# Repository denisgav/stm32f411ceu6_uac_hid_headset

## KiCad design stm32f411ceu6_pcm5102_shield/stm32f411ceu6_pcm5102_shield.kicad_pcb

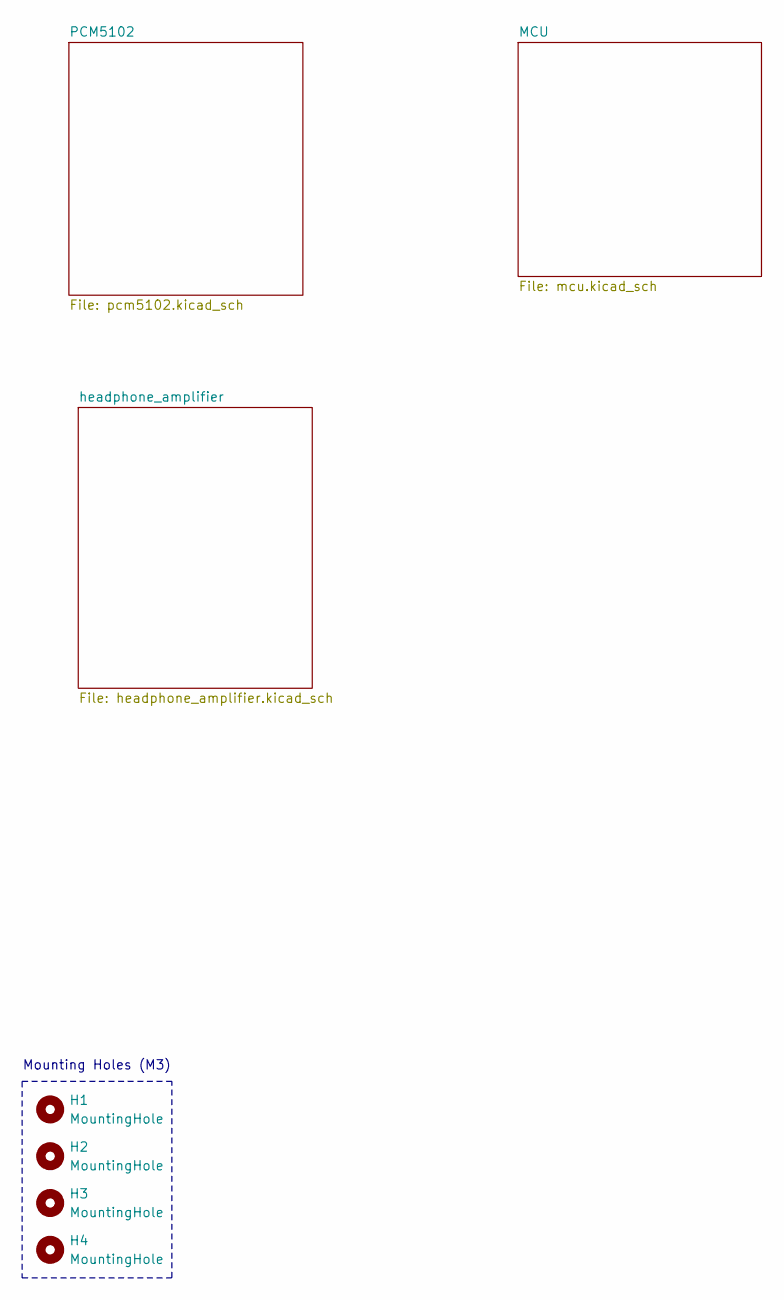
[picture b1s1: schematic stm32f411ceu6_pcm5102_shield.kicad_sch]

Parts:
H1, H2, H3, H4: MountingHole; MountingHole_3.2mm_M3

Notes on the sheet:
Mounting Holes (M3)

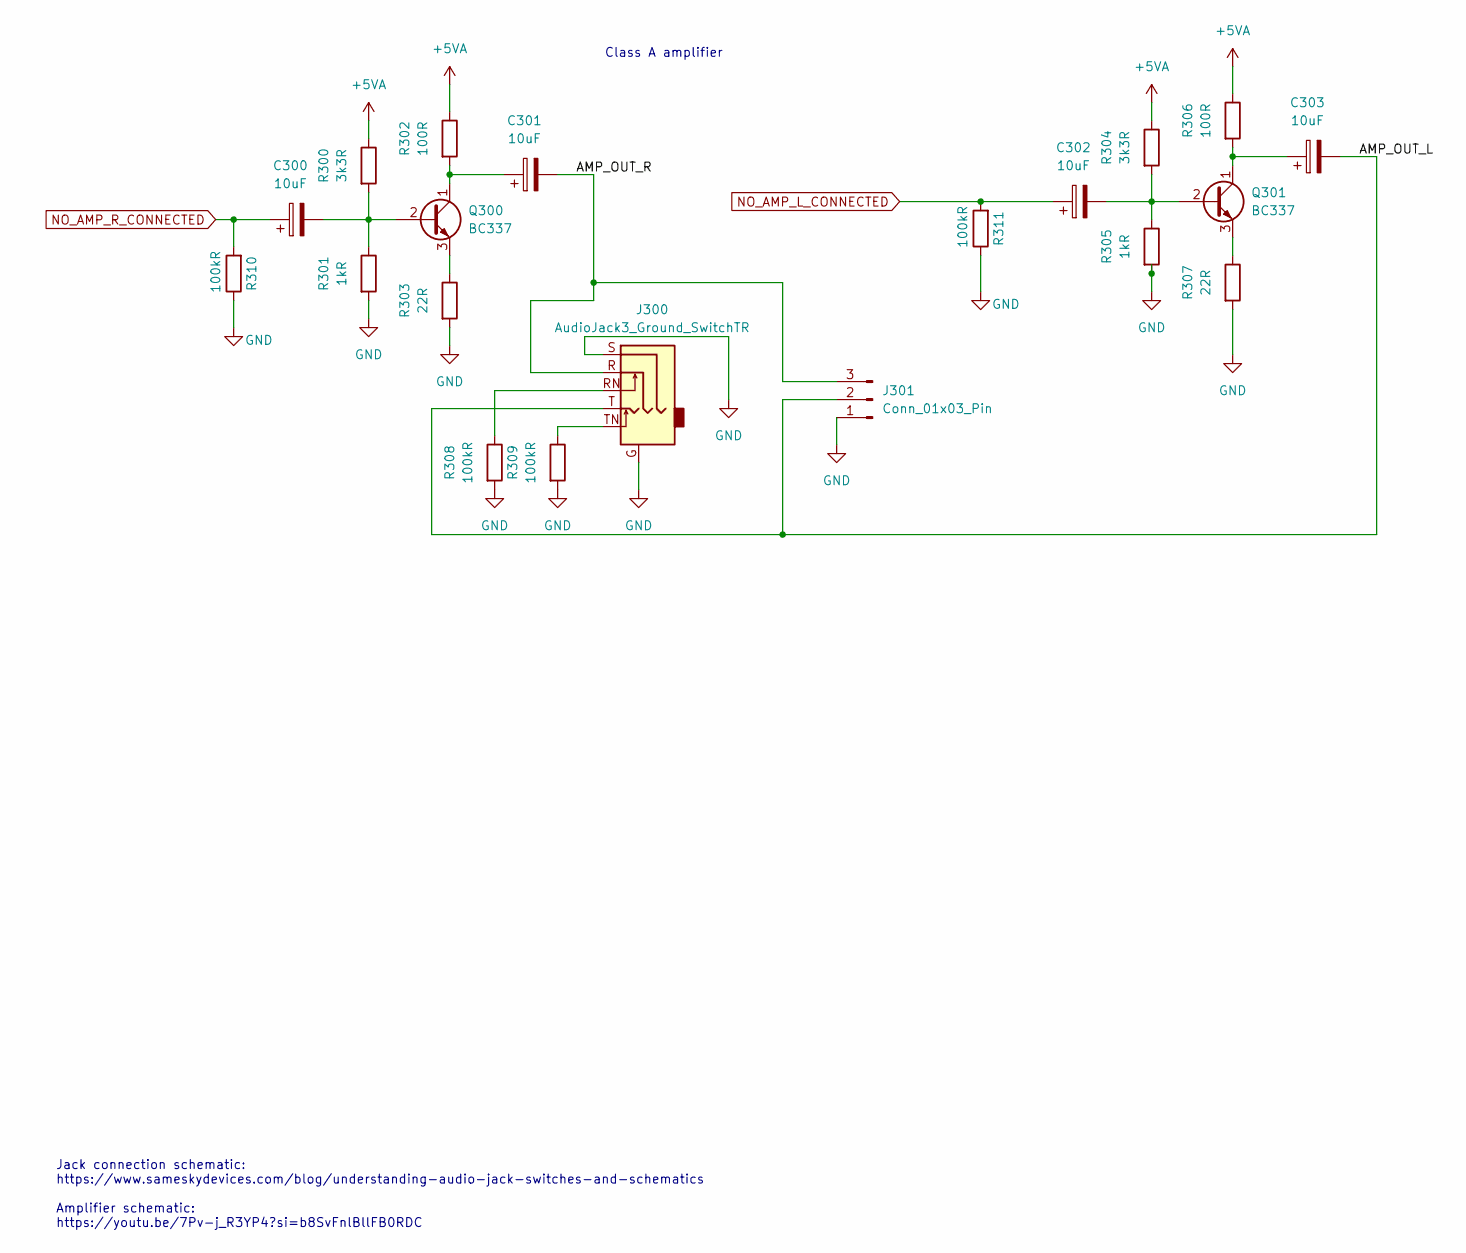
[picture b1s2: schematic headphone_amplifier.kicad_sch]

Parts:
C300, C301, C302, C303: 10uF; CP_EIA-3216-18_Kemet-A; Manufacturer Part Number TAJA106K016RNJ
J300: AudioJack3_Ground_SwitchTR; AudioJack_3.5mm_PJ311
J301: Conn_01x03_Pin; PinHeader_1x03_P2.54mm_Vertical
Q300, Q301: BC337; TO-92_Inline; Manufacturer Part Number LGE BC337-40
R300, R304: 3k3R; R_0805_2012Metric; Manufacturer Part Number 0805W8F3301T5E
R301, R305: 1kR; R_0805_2012Metric; Manufacturer Part Number 0805W8F1001T5E
R302, R306: 100R; R_0805_2012Metric; Manufacturer Part Number 0805W8F1000T5E
R303, R307: 22R; R_0603_1608Metric; Manufacturer Part Number 0603WAF220JT5E
R308, R309, R310, R311: 100kR; R_0805_2012Metric; Manufacturer Part Number 0805W8J0104T5E

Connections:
+5VA: R300.1, R302.1, R304.1, R306.1; also elsewhere on the board
/headphone_amplifier/AMP_OUT_L: C303.2, J300.T, J301.2
/headphone_amplifier/AMP_OUT_R: C301.2, J300.R, J301.3
GND: J300.G, J300.S, J301.1, R301.2, R303.2, R305.2, R307.2, R308.2, R309.2, R310.1, R311.1; also elsewhere on the board
NO_AMP_L_CONNECTED: C302.1, R311.2; also elsewhere on the board
NO_AMP_R_CONNECTED: C300.1, R310.2; also elsewhere on the board
unnamed: J300.RN, R308.1
unnamed: J300.TN, R309.1
unnamed: C300.2, Q300.2 (B), R300.2, R301.1
unnamed: C301.1, Q300.1 (C), R302.2
unnamed: Q300.3 (E), R303.1
unnamed: C302.2, Q301.2 (B), R304.2, R305.1
unnamed: C303.1, Q301.1 (C), R306.2
unnamed: Q301.3 (E), R307.1

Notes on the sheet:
Jack connection schematic: https://www.sameskydevices.com/blog/understanding-audio-jack-switches-and-schematics Amplifier schematic: https://youtu.be/7Pv-j_R3YP4?si=b8SvFnlBllFB0RDC
Class A amplifier

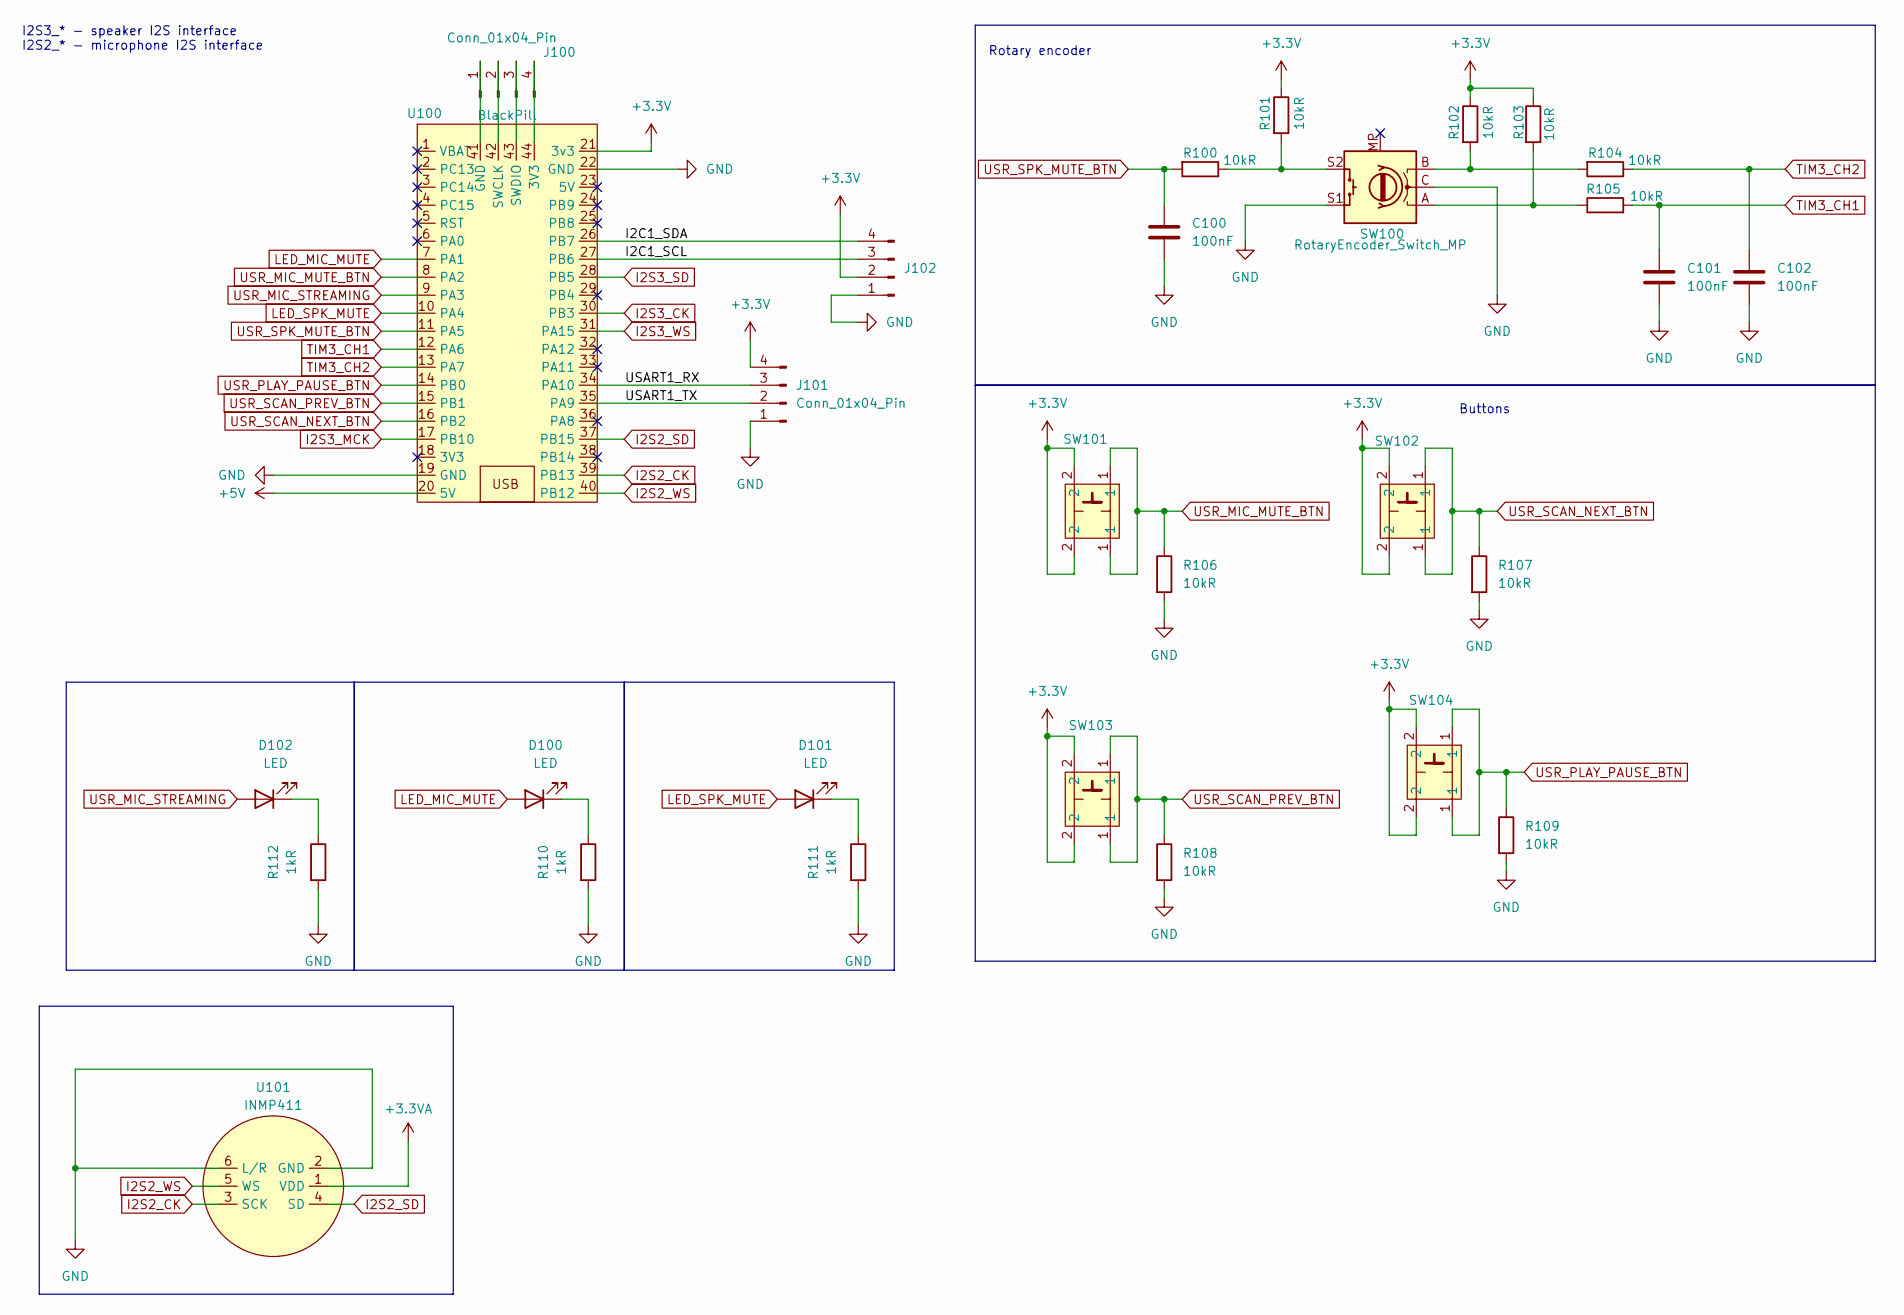
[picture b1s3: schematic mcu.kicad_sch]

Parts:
C100, C101, C102: 100nF; C_0402_1005Metric; Manufacturer Part Number CL05B104KO5NNNC
D100, D101, D102: LED; LED_D3.0mm
J100, J101, J102: Conn_01x04_Pin; PinHeader_1x04_P2.54mm_Vertical
R100, R101, R102, R103, R104, R105: 10kR; R_0805_2012Metric; Manufacturer Part Number 0805W8J0103T5E
R106, R107, R108, R109: 10kR; R_0805_2012Metric; Manufacturer Part Number 0805W8J0103T5E; DigiKey Part Number 1276-3431-6-ND
R110, R111, R112: 1kR; R_0805_2012Metric; Manufacturer Part Number 0805W8F1001T5E
SW100: RotaryEncoder_Switch_MP; RotaryEncoder_Alps_EC12E-Switch_Vertical_H20mm
SW101, SW102, SW103, SW104: SW_PUSH_6mm_H5mm
U100: BlackPill; stm32f411_blackpill
U101: INMP411; inmp441

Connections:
+3.3V: J101.4, J102.2, R101.1, R102.1, R103.1, SW101.2, SW102.2, SW103.2, SW104.2, U100.21 (3v3); also elsewhere on the board
+3.3VA: U101.1 (VDD); also elsewhere on the board
+5V: U100.20 (5V); also elsewhere on the board
/MCU/I2C1_SCL: J102.3, U100.27 (PB6)
/MCU/I2C1_SDA: J102.4, U100.26 (PB7)
/MCU/USART1_RX: J101.3, U100.34 (PA10)
/MCU/USART1_TX: J101.2, U100.35 (PA9)
GND: C100.2, C101.2, C102.2, J101.1, J102.1, R106.2, R107.2, R108.2, R109.2, R110.2, R111.2, R112.2, SW100.C, SW100.S1, U100.19 (GND), U100.22 (GND), U101.2 (GND), U101.6 (L/R); also elsewhere on the board
I2S2_CK: U100.39 (PB13), U101.3 (SCK)
I2S2_SD: U100.37 (PB15), U101.4 (SD)
I2S2_WS: U100.40 (PB12), U101.5 (WS)
I2S3_CK: U100.30 (PB3); also elsewhere on the board
I2S3_MCK: U100.17 (PB10); also elsewhere on the board
I2S3_SD: U100.28 (PB5); also elsewhere on the board
I2S3_WS: U100.31 (PA15); also elsewhere on the board
LED_MIC_MUTE: D100.2 (A), U100.7 (PA1)
LED_SPK_MUTE: D101.2 (A), U100.10 (PA4)
unnamed: D100.1 (K), R110.1
unnamed: D101.1 (K), R111.1
unnamed: D102.1 (K), R112.1
unnamed: J100.1, U100.41 (GND)
unnamed: J100.2, U100.42 (SWCLK)
unnamed: J100.3, U100.43 (SWDIO)
unnamed: J100.4, U100.44 (3V3)
unnamed: R100.1, R101.2, SW100.S2
unnamed: R102.2, R104.2, SW100.B
unnamed: R103.2, R105.1, SW100.A
TIM3_CH1: C101.1, R105.2, U100.12 (PA6)
TIM3_CH2: C102.1, R104.1, U100.13 (PA7)
USR_MIC_MUTE_BTN: R106.1, SW101.1, U100.8 (PA2)
USR_MIC_STREAMING: D102.2 (A), U100.9 (PA3)
USR_PLAY_PAUSE_BTN: R109.1, SW104.1, U100.14 (PB0)
USR_SCAN_NEXT_BTN: R107.1, SW102.1, U100.16 (PB2)
USR_SCAN_PREV_BTN: R108.1, SW103.1, U100.15 (PB1)
USR_SPK_MUTE_BTN: C100.1, R100.2, U100.11 (PA5)

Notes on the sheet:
Rotary encoder
Buttons
I2S3_* - speaker I2S interface I2S2_* - microphone I2S interface

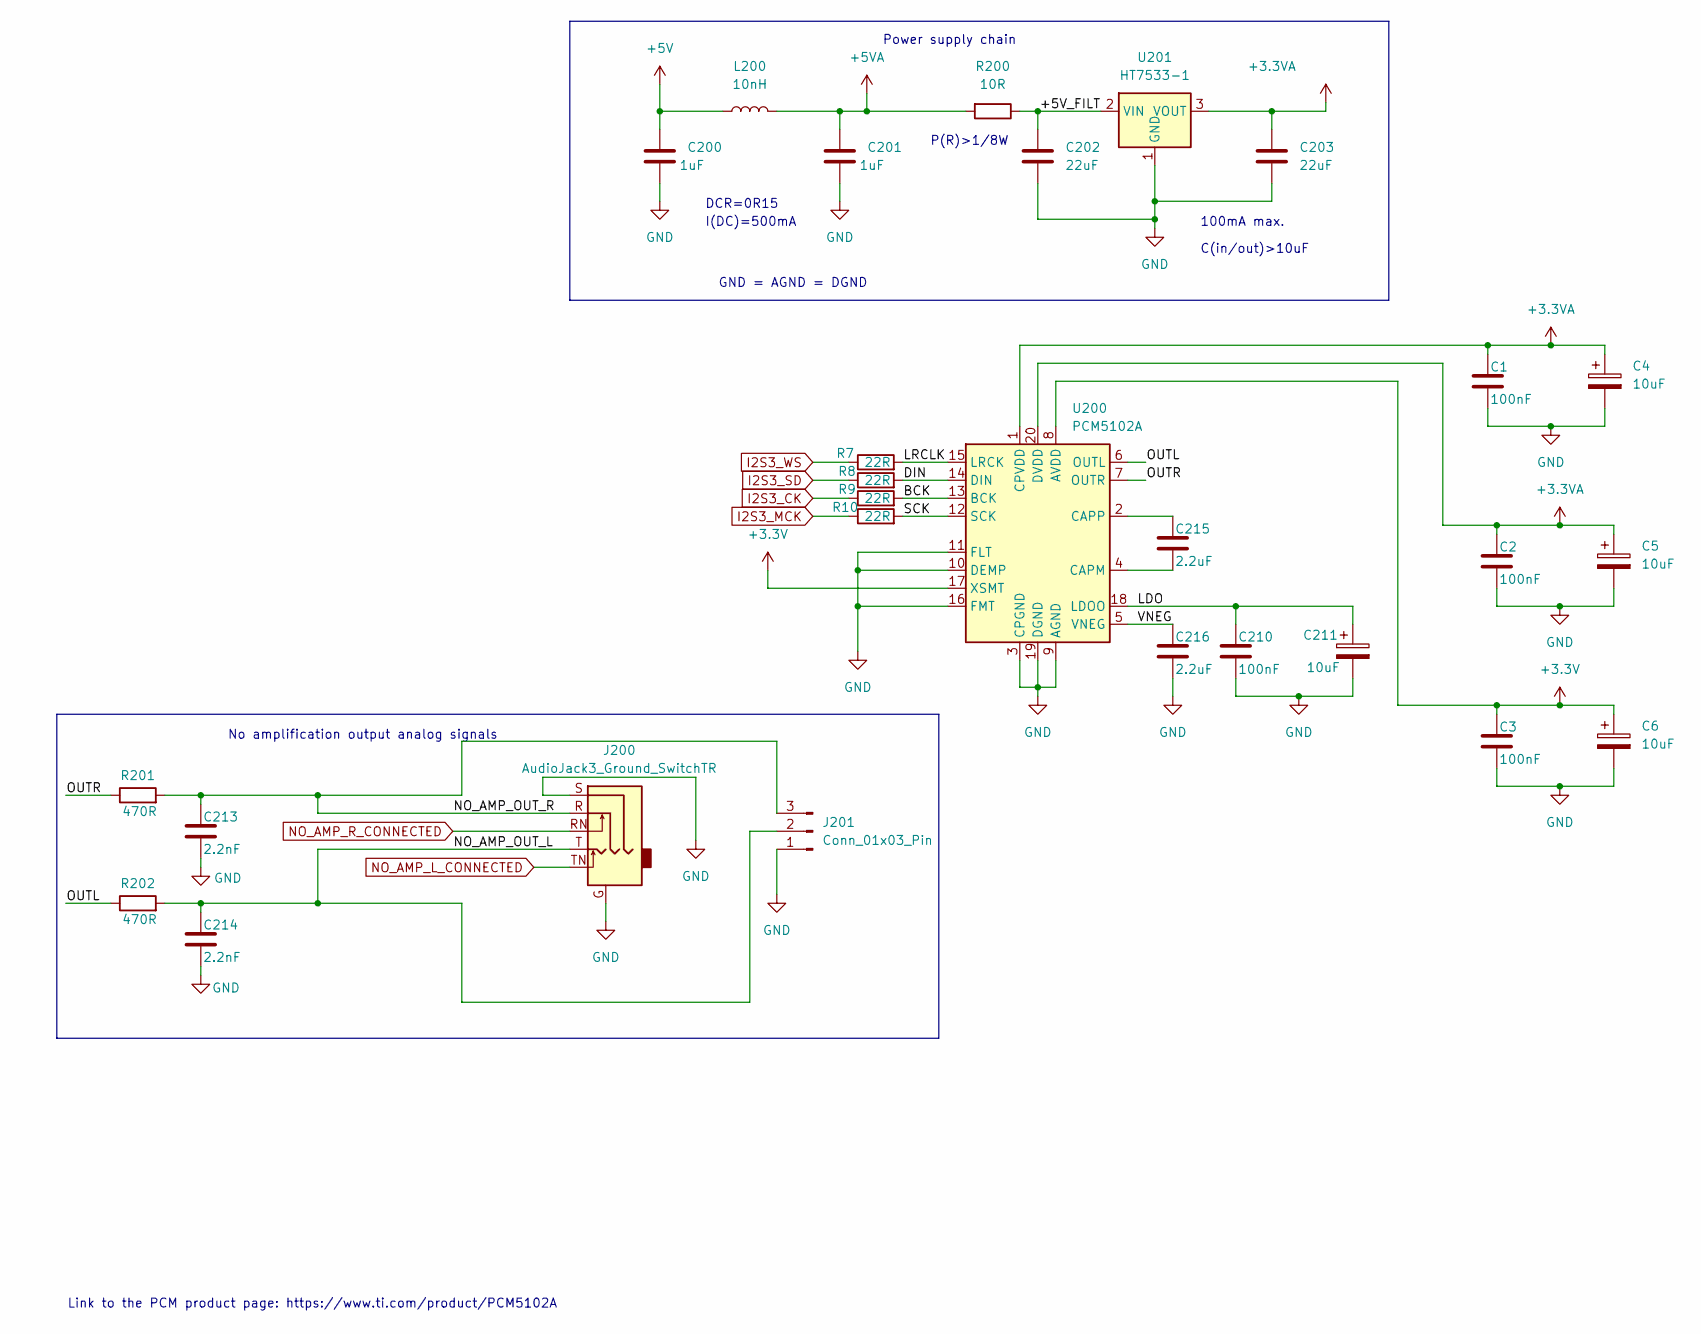
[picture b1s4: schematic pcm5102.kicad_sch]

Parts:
C1, C2, C3, C210: 100nF; C_0402_1005Metric; Manufacturer Part Number CL05B104KO5NNNC
C4, C5, C6, C211: 10uF; CP_EIA-3216-18_Kemet-A; Manufacturer Part Number TAJA106K016RNJ
C200, C201: 1uF; C_0805_2012Metric; Manufacturer Part Number CL21B105KBFNNNE
C202, C203: 22uF; C_0805_2012Metric; Manufacturer Part Number CL21A226MQQNNNE
C213, C214: 2.2nF; C_0805_2012Metric; Manufacturer Part Number CL21C222JBFNNNE
C215, C216: 2.2uF; C_0805_2012Metric; Manufacturer Part Number CL21B225KAFNNNE
J200: AudioJack3_Ground_SwitchTR; AudioJack_3.5mm_PJ311
J201: Conn_01x03_Pin; PinHeader_1x03_P2.54mm_Vertical
L200: 10nH; L_0402_1005Metric; Manufacturer Part Number CGA2B3X7R1H103M050BE
R7, R8, R9, R10: 22R; R_0603_1608Metric; Manufacturer Part Number 0603WAF220JT5E
R200: 10R; R_0805_2012Metric; Manufacturer Part Number 0805W8F100JT5E
R201, R202: 470R; R_0805_2012Metric; Manufacturer Part Number 0805W8F4700T5E
U200: PCM5102A; TSSOP-20_4.4x6.5mm_P0.65mm
U201: HT7533-1; SOT-89-3; Manufacturer Part Number HT7533-1

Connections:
+3.3V: C3.1, C6.1, U200.8 (AVDD), U200.17 (XSMT); also elsewhere on the board
+3.3VA: C1.1, C2.1, C4.1, C5.1, C203.1, U200.1 (CPVDD), U200.20 (DVDD), U201.3 (VOUT); also elsewhere on the board
+5V: C200.1, L200.1; also elsewhere on the board
+5VA: C201.1, L200.2, R200.2; also elsewhere on the board
/PCM5102/+5V_FILT: C202.1, R200.1, U201.2 (VIN)
/PCM5102/BCK: R9.2, U200.13 (BCK)
/PCM5102/DIN: R8.2, U200.14 (DIN)
/PCM5102/LDO: C210.1, C211.1, U200.18 (LDOO)
/PCM5102/LRCLK: R7.2, U200.15 (LRCK)
/PCM5102/NO_AMP_OUT_L: C214.1, J200.T, J201.2, R202.2
/PCM5102/NO_AMP_OUT_R: C213.1, J200.R, J201.3, R201.2
/PCM5102/OUTL: R202.1, U200.6 (OUTL)
/PCM5102/OUTR: R201.1, U200.7 (OUTR)
/PCM5102/SCK: R10.2, U200.12 (SCK)
/PCM5102/VNEG: C216.1, U200.5 (VNEG)
GND: C1.2, C2.2, C3.2, C4.2, C5.2, C6.2, C200.2, C201.2, C202.2, C203.2, C210.2, C211.2, C213.2, C214.2, C216.2, J200.G, J200.S, J201.1, U200.3 (CPGND), U200.9 (AGND), U200.10 (DEMP), U200.11 (FLT), U200.16 (FMT), U200.19 (DGND), U201.1 (GND); also elsewhere on the board
I2S3_CK: R9.1; also elsewhere on the board
I2S3_MCK: R10.1; also elsewhere on the board
I2S3_SD: R8.1; also elsewhere on the board
I2S3_WS: R7.1; also elsewhere on the board
NO_AMP_L_CONNECTED: J200.TN; also elsewhere on the board
NO_AMP_R_CONNECTED: J200.RN; also elsewhere on the board
unnamed: C215.2, U200.4 (CAPM)
unnamed: C215.1, U200.2 (CAPP)

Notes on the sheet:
100mA max.
GND = AGND = DGND
DCR=0R15
C(in/out)>10uF
Link to the PCM product page: https://www.ti.com/product/PCM5102A
P(R)>1/8W
I(DC)=500mA
No amplification output analog signals
Power supply chain

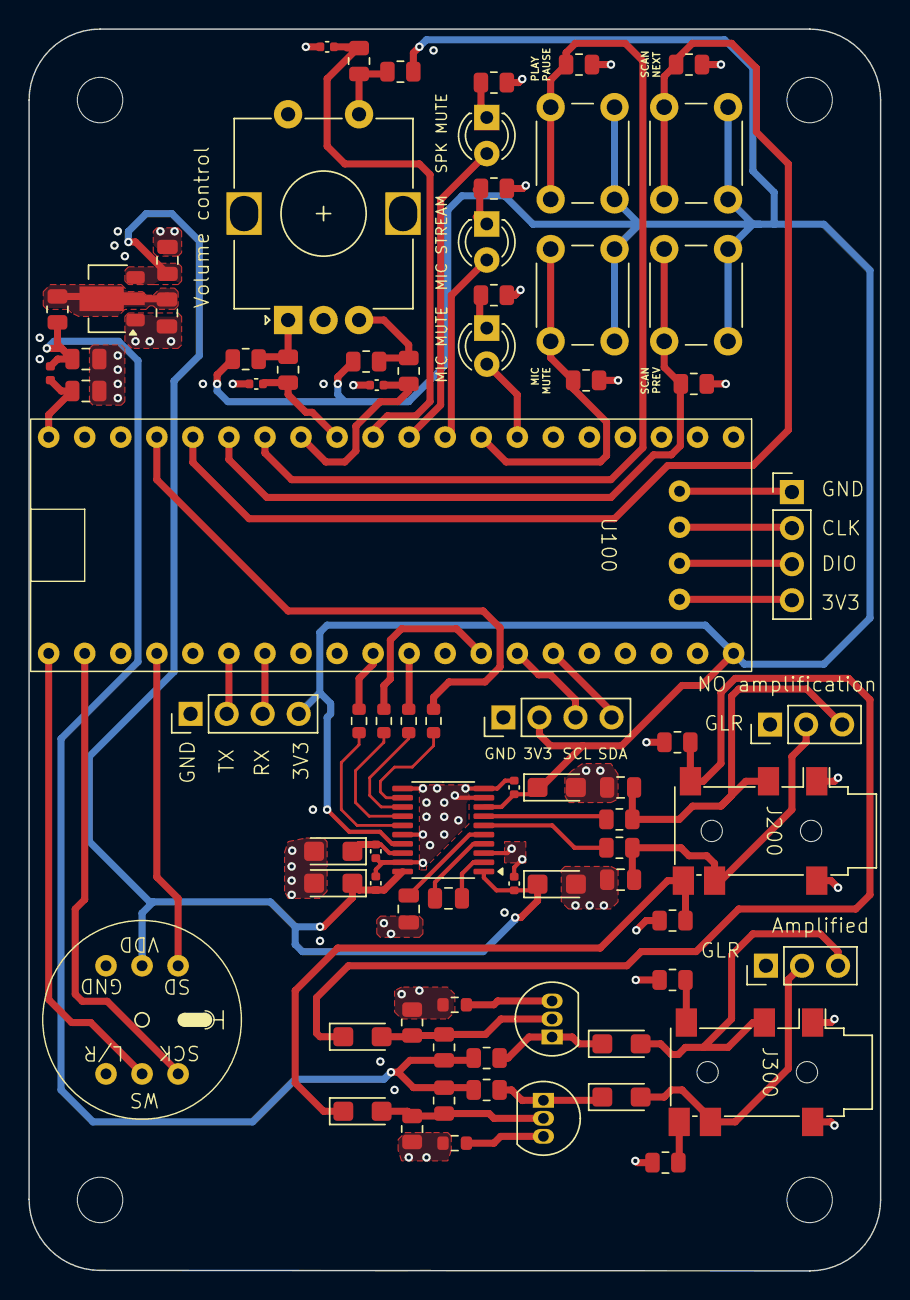
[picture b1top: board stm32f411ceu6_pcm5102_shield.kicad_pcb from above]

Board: 4 copper layers, 60.0 x 87.5 mm, 81 parts (0 on the bottom side), 61 nets.

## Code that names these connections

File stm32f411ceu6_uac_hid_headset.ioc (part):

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Mcu.Name=STM32F411C(C-E)Ux
Mcu.Package=UFQFPN48
Mcu.UserName=STM32F411CEUx
PA1.GPIOParameters=GPIO_Label
PA1.GPIO_Label=LED_MIC_MUTE
PA1.Signal=GPIO_Output
PA10.Mode=Asynchronous
PA10.Signal=USART1_RX
PA11.Mode=Device_Only
PA11.Signal=USB_OTG_FS_DM
PA12.Mode=Device_Only
PA12.Signal=USB_OTG_FS_DP
PA13.Mode=Serial_Wire
PA13.Signal=SYS_JTMS-SWDIO
PA14.Mode=Serial_Wire
PA14.Signal=SYS_JTCK-SWCLK
PA15.Mode=Half_Duplex_Master
PA15.Signal=I2S3_WS
PA2.GPIOParameters=GPIO_PuPd,GPIO_Label
PA2.GPIO_Label=USR_MIC_MUTE_BTN
PA2.GPIO_PuPd=GPIO_PULLDOWN
PA2.Signal=GPIO_Input
PA3.GPIOParameters=GPIO_Label
PA3.GPIO_Label=LED_MIC_STREAMING
PA3.Signal=GPIO_Output
PA4.GPIOParameters=GPIO_Label
PA4.GPIO_Label=LED_SPK_MUTE
PA4.Signal=GPIO_Output
PA5.GPIOParameters=GPIO_PuPd,GPIO_Label
PA5.GPIO_Label=USR_SPK_MUTE_BTN
PA5.GPIO_PuPd=GPIO_PULLUP
PA5.Signal=GPIO_Input
PA6.Signal=S_TIM3_CH1
PA7.Signal=S_TIM3_CH2
PA9.Mode=Asynchronous
PA9.Signal=USART1_TX
PB0.GPIOParameters=GPIO_PuPd,GPIO_Label
PB0.GPIO_Label=USR_PLAY_PAUSE_BTN
PB0.GPIO_PuPd=GPIO_PULLDOWN
PB0.Signal=GPIO_Input
PB1.GPIOParameters=GPIO_PuPd,GPIO_Label
PB1.GPIO_Label=USR_SCAN_PREV_BTN
PB1.GPIO_PuPd=GPIO_PULLDOWN
PB1.Signal=GPIO_Input
PB10.Mode=Master_Clock_Activated
PB10.Signal=I2S3_MCK
PB12.Mode=Half_Duplex_Master
PB12.Signal=I2S2_WS
PB13.Mode=Half_Duplex_Master
PB13.Signal=I2S2_CK
PB15.Mode=Half_Duplex_Master
PB15.Signal=I2S2_SD
PB2.GPIOParameters=GPIO_PuPd,GPIO_Label
PB2.GPIO_Label=USR_SCAN_NEXT_BTN
PB2.GPIO_PuPd=GPIO_PULLDOWN
PB2.Signal=GPIO_Input
PB3.Mode=Half_Duplex_Master
PB3.Signal=I2S3_CK
PB5.Mode=Half_Duplex_Master
PB5.Signal=I2S3_SD
PB6.Mode=I2C
PB6.Signal=I2C1_SCL
PB7.Mode=I2C
PB7.Signal=I2C1_SDA
PC13-ANTI_TAMP.GPIOParameters=GPIO_Label
PC13-ANTI_TAMP.GPIO_Label=ONBOARD_LED
PC13-ANTI_TAMP.Signal=GPIO_Output
PH0\ -\ OSC_IN.Mode=HSE-External-Oscillator
PH0\ -\ OSC_IN.Signal=RCC_OSC_IN
PH1\ -\ OSC_OUT.Mode=HSE-External-Oscillator
PH1\ -\ OSC_OUT.Signal=RCC_OSC_OUT
RCC.HSE_VALUE=25000000
RCC.SYSCLKFreq_VALUE=84000000
RCC.SYSCLKSource=RCC_SYSCLKSOURCE_PLLCLK
board=custom

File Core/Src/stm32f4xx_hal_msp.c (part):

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
    __HAL_RCC_GPIOB_CLK_ENABLE();
    /**I2C1 GPIO Configuration
    PB6     ------> I2C1_SCL
    PB7     ------> I2C1_SDA
    */
    GPIO_InitStruct.Pin = GPIO_PIN_6|GPIO_PIN_7;
    GPIO_InitStruct.Mode = GPIO_MODE_AF_OD;
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    __HAL_RCC_I2C1_CLK_DISABLE();

    /**I2C1 GPIO Configuration
    PB6     ------> I2C1_SCL
    PB7     ------> I2C1_SDA
    */
    HAL_GPIO_DeInit(GPIOB, GPIO_PIN_6);

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
    __HAL_RCC_GPIOB_CLK_ENABLE();
    /**I2S2 GPIO Configuration
    PB12     ------> I2S2_WS
    PB13     ------> I2S2_CK
    PB15     ------> I2S2_SD
    */
    GPIO_InitStruct.Pin = GPIO_PIN_12|GPIO_PIN_13|GPIO_PIN_15;
    GPIO_InitStruct.Mode = GPIO_MODE_AF_PP;
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    __HAL_RCC_GPIOB_CLK_ENABLE();
    __HAL_RCC_GPIOA_CLK_ENABLE();
    /**I2S3 GPIO Configuration
    PB10     ------> I2S3_MCK
    PA15     ------> I2S3_WS
    PB3     ------> I2S3_CK
    PB5     ------> I2S3_SD
    */
    GPIO_InitStruct.Pin = GPIO_PIN_10|GPIO_PIN_3|GPIO_PIN_5;
    GPIO_InitStruct.Mode = GPIO_MODE_AF_PP;
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    __HAL_RCC_SPI2_CLK_DISABLE();

    /**I2S2 GPIO Configuration
    PB12     ------> I2S2_WS
    PB13     ------> I2S2_CK
    PB15     ------> I2S2_SD
    */
    HAL_GPIO_DeInit(GPIOB, GPIO_PIN_12|GPIO_PIN_13|GPIO_PIN_15);

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    __HAL_RCC_SPI3_CLK_DISABLE();

    /**I2S3 GPIO Configuration
    PB10     ------> I2S3_MCK
    PA15     ------> I2S3_WS
    PB3     ------> I2S3_CK
    PB5     ------> I2S3_SD
    */
    HAL_GPIO_DeInit(GPIOB, GPIO_PIN_10|GPIO_PIN_3|GPIO_PIN_5);

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
    __HAL_RCC_GPIOA_CLK_ENABLE();
    /**TIM3 GPIO Configuration
    PA6     ------> TIM3_CH1
    PA7     ------> TIM3_CH2
    */
    GPIO_InitStruct.Pin = GPIO_PIN_6|GPIO_PIN_7;
    GPIO_InitStruct.Mode = GPIO_MODE_AF_PP;
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    __HAL_RCC_TIM3_CLK_DISABLE();

    /**TIM3 GPIO Configuration
    PA6     ------> TIM3_CH1
    PA7     ------> TIM3_CH2
    */
    HAL_GPIO_DeInit(GPIOA, GPIO_PIN_6|GPIO_PIN_7);

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
    __HAL_RCC_GPIOA_CLK_ENABLE();
    /**USART1 GPIO Configuration
    PA9     ------> USART1_TX
    PA10     ------> USART1_RX
    */
    GPIO_InitStruct.Pin = GPIO_PIN_9|GPIO_PIN_10;
    GPIO_InitStruct.Mode = GPIO_MODE_AF_PP;
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    __HAL_RCC_USART1_CLK_DISABLE();

    /**USART1 GPIO Configuration
    PA9     ------> USART1_TX
    PA10     ------> USART1_RX
    */
    HAL_GPIO_DeInit(GPIOA, GPIO_PIN_9|GPIO_PIN_10);

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
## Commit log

2024-12-30 Add Kicad scheme
2024-12-30 Headphone amplifier, black pill footprint & symbol
2024-12-31 Headphone jack detection
2024-12-31 Placed all components on the board
2025-01-01 Add rotary encoder
2025-01-01 Alignment of ST project to the scheme
2025-01-01 Items numeration fix
2025-01-02 BOM updates
2025-01-02 Put all items on a board
2025-01-02 PCB rules setup
2025-01-02 Initial layout
2025-01-03 Board outline
2025-01-03 First PCB routing
2025-01-04 Update firmware to simplify routing
2025-01-04 BOM fixes
2025-01-05 Add 3D model for audio jack

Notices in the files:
Core/Src/stm32f4xx_hal_msp.c:
Copyright (c) 2024 STMicroelectronics.
All rights reserved.
This software is licensed under terms that can be found in the LICENSE file
